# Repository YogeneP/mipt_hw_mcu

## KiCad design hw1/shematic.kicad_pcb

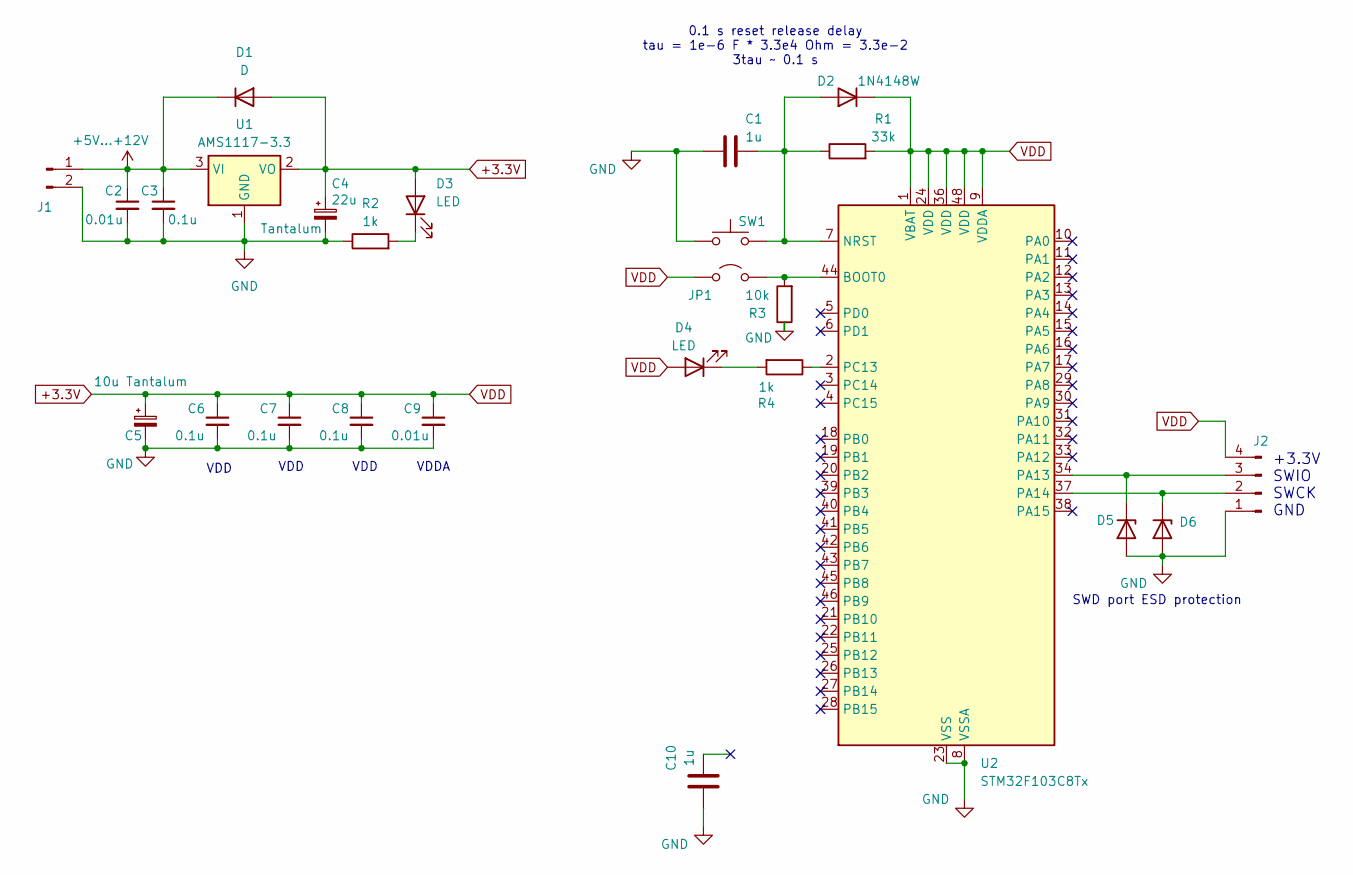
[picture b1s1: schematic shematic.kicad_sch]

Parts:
C1, C10: 1u; C_1206_3216Metric_Pad1.33x1.80mm_HandSolder
C2, C9: 0.01u; C_1206_3216Metric_Pad1.33x1.80mm_HandSolder
C3, C6, C7, C8: 0.1u; C_1206_3216Metric_Pad1.33x1.80mm_HandSolder
C4: 22u; CP_EIA-3528-12_Kemet-T_HandSolder
C5: 10u Tantalum; CP_EIA-3528-12_Kemet-T_HandSolder
D1: D; Nexperia_CFP3_SOD-123W
D2: 1N4148W; D_1206_3216Metric_Pad1.42x1.75mm_HandSolder
D3, D4: LED; LED_1206_3216Metric_Pad1.42x1.75mm_HandSolder
D5, D6: PESD5V0L1UL; D_SOD-882
J1: Conn_01x02_Pin; PinHeader_1x02_P2.54mm_Horizontal
J2: Conn_01x04_Pin; PinHeader_1x04_P2.54mm_Vertical
JP1: Jumper_2_Open; PinHeader_1x02_P1.00mm_Vertical
R1: 33k; R_1206_3216Metric_Pad1.30x1.75mm_HandSolder
R2, R4: 1k; R_1206_3216Metric_Pad1.30x1.75mm_HandSolder
R3: 10k; R_1206_3216Metric_Pad1.30x1.75mm_HandSolder
SW1: SW_MEC_5G; SW_PUSH_6mm
U1: AMS1117-3.3; SOT-223-3_TabPin2
U2: STM32F103C8Tx; LQFP-48_7x7mm_P0.5mm

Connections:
+3.3V: C4.1, C5.1, C6.1, C7.1, C8.1, C9.1, D1.2 (A), D2.1 (K), D3.2 (A), D4.2 (A), J2.4, JP1.1 (A), R1.2, U1.2 (VO), U2.1 (VBAT), U2.9 (VDDA), U2.24 (VDD), U2.36 (VDD), U2.48 (VDD)
+5V...+12V: C2.1, C3.1, D1.1 (K), J1.1, U1.3 (VI)
GND: C1.1, C2.2, C3.2, C4.2, C5.2, C6.2, C7.2, C8.2, C9.2, C10.1, D5.2 (A), D6.2 (A), J1.2, J2.1, R2.1, R3.1, SW1.1 (A), U1.1 (GND), U2.8 (VSSA), U2.23 (VSS), U2.35 (VSS), U2.47 (VSS)
unnamed: C1.2, D2.2 (A), R1.1, SW1.2 (B), U2.7 (NRST)
unnamed: D3.1 (K), R2.2
unnamed: D4.1 (K), R4.2
unnamed: D5.1 (K), J2.3, U2.34 (PA13)
unnamed: D6.1 (K), J2.2, U2.37 (PA14)
unnamed: JP1.2 (B), R3.2, U2.44 (BOOT0)
unnamed: R4.1, U2.2 (PC13)

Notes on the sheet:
VDD
VDDA
+3.3V SWIO SWCK GND
0.1 s reset release delay tau = 1e-6 F * 3.3e4 Ohm = 3.3e-2 3tau ~ 0.1 s
SWD port ESD protection

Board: 2 copper layers, 26 parts (0 on the bottom side), 10 nets, no tracks yet.
